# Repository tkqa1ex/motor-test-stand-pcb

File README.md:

# Motor Test Stand PCB

This repository contains the PCB design for a DC motor test stand.

## Features
- Current measurement (INA219 / ACS758)
- Temperature sensing (TMP117)
- Microcontroller interface (Arduino)

## Project Goal
Measure torque, efficiency, and electrical parameters of a DC motor using a generator-based load system.

## Files
- /pcb → PCB layout
- /schematic → circuit design
- /gerbers → manufacturing files

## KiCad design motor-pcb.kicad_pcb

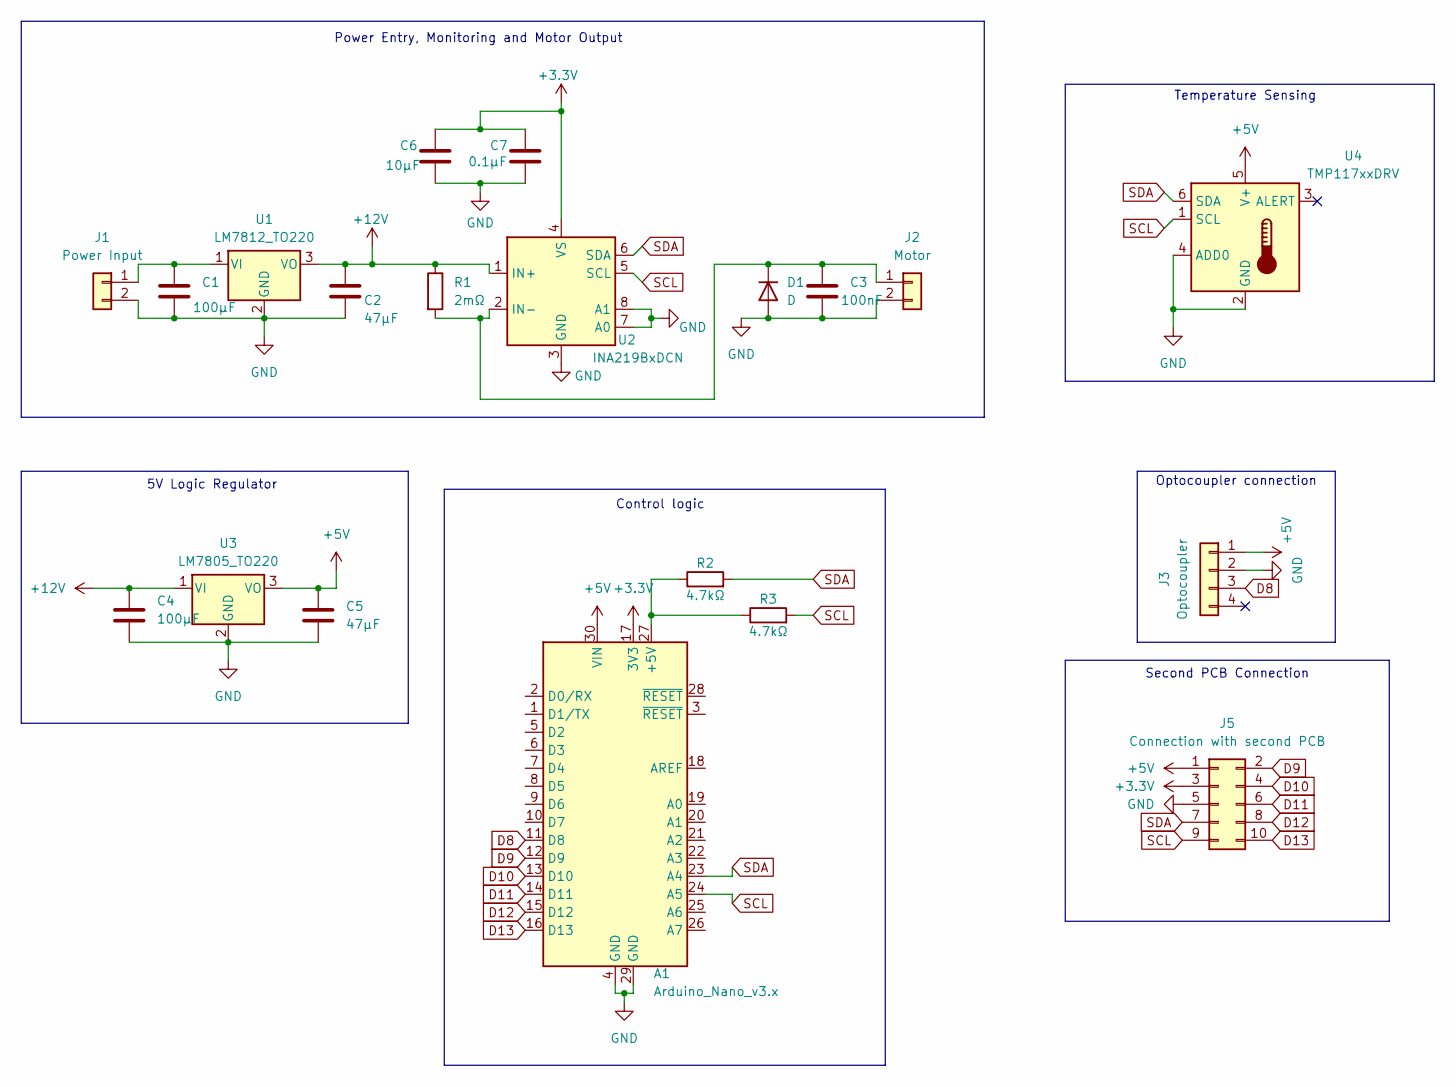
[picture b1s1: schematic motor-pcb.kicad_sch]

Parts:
A1: Arduino_Nano_v3.x; Arduino_Nano
C1, C4: 100µF; CP_Radial_D6.3mm_P2.50mm
C2, C5: 47µF; CP_Radial_D6.3mm_P2.50mm
C3: 100nF; C_Disc_D5.0mm_W2.5mm_P2.50mm
C6: 10µF; C_0805_2012Metric_Pad1.18x1.45mm_HandSolder
C7: 0.1µF; C_0805_2012Metric_Pad1.18x1.45mm_HandSolder
D1: D; D_DO-41_SOD81_P10.16mm_Horizontal
J1: Power Input; TerminalBlock_CUI_TB007-508-02_1x02_P5.08mm_Horizontal
J2: Motor; TerminalBlock_CUI_TB007-508-02_1x02_P5.08mm_Horizontal
J3: Optocoupler; PinHeader_1x04_P2.54mm_Vertical
J5: Connection with second PCB; PinHeader_2x05_P2.54mm_Vertical
R1: 2mΩ; R_2512_6332Metric_Pad1.40x3.35mm_HandSolder
R2, R3: 4.7kΩ; R_Axial_DIN0207_L6.3mm_D2.5mm_P7.62mm_Horizontal
U1: LM7812_TO220; TO-220-3_Vertical
U2: INA219BxDCN; SOT-23-8
U3: LM7805_TO220; TO-220-3_Vertical
U4: TMP117xxDRV; WSON-6-1EP_2x2mm_P0.65mm_EP1x1.6mm

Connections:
+3.3V: A1.17 (3V3), C6.1, C7.1, J5.3, U2.4 (VS)
+5V: A1.30 (VIN), C5.1, J3.1, J5.1, U3.3 (VO), U4.5 (V+)
+12V: C2.1, C4.1, R1.1, U1.3 (VO), U2.1 (IN+), U3.1 (VI)
D8: A1.11 (D8), J3.3
D9: A1.12 (D9), J5.2
D10: A1.13 (D10), J5.4
D11: A1.14 (D11), J5.6
D12: A1.15 (D12), J5.8
D13: A1.16 (D13), J5.10
GND: A1.4 (GND), A1.29 (GND), C1.2, C2.2, C3.2, C4.2, C5.2, C6.2, C7.2, D1.2 (A), J1.2, J2.2, J3.2, J5.5, U1.2 (GND), U2.3 (GND), U2.7 (A0), U2.8 (A1), U3.2 (GND), U4.2 (GND), U4.4 (ADD0)
unnamed: A1.27 (+5V), R2.1, R3.1
unnamed: C3.1, D1.1 (K), J2.1, R1.2, U2.2 (IN-)
unnamed: C1.1, J1.1, U1.1 (VI)
SCL: A1.24 (A5), J5.9, R3.2, U2.5 (SCL), U4.1 (SCL)
SDA: A1.23 (A4), J5.7, R2.2, U2.6 (SDA), U4.6 (SDA)

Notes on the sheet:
Temperature Sensing
Control logic
Optocoupler connection
Power Entry, Monitoring and Motor Output
Second PCB Connection
5V Logic Regulator

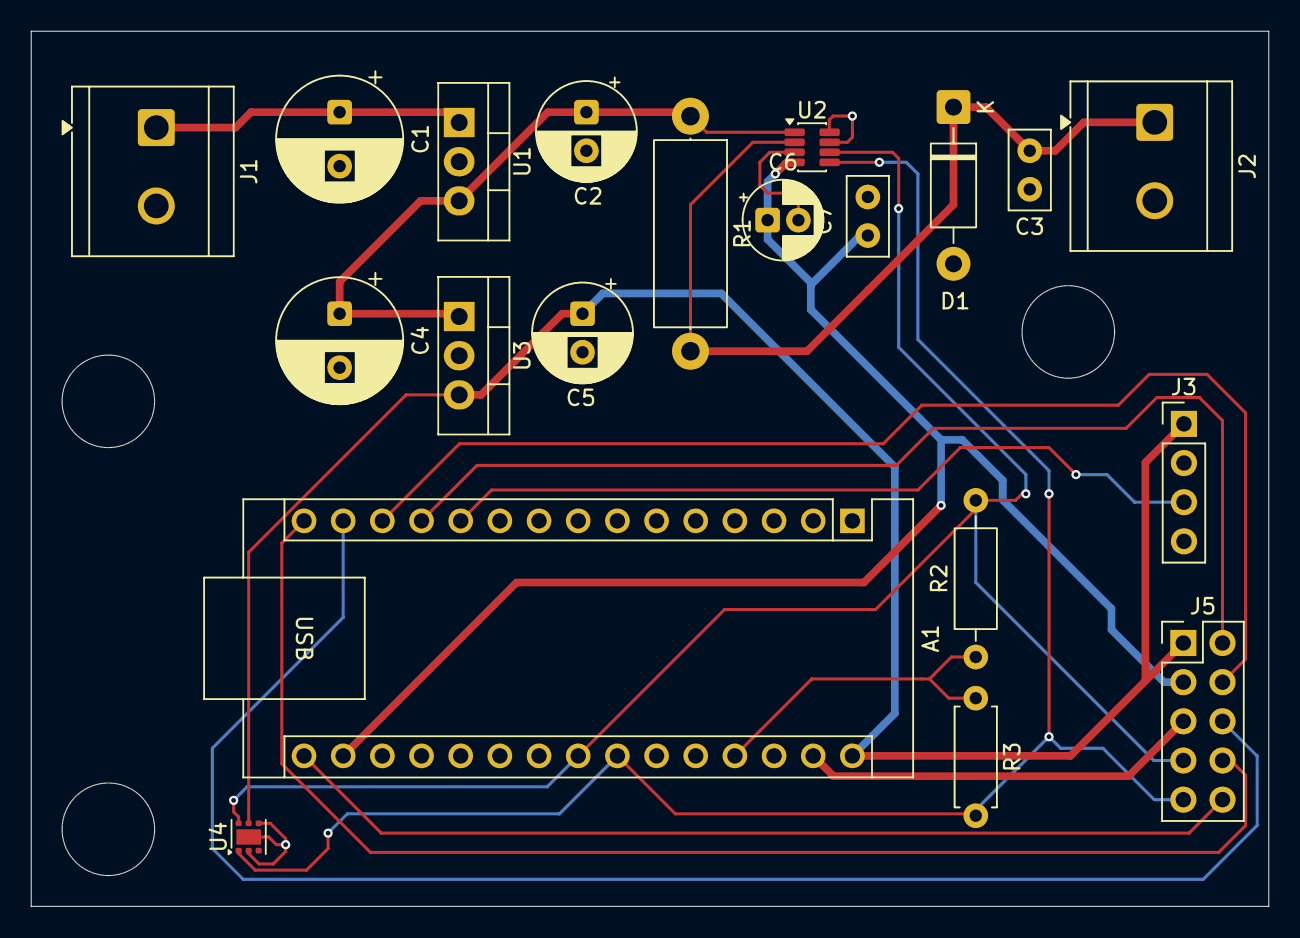
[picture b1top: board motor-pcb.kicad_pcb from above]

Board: 2 copper layers, 80.2 x 56.8 mm, 20 parts (0 on the bottom side), 15 nets.

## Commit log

2026-05-03 Update README with project information and features
    Added project details and features to README.
2026-05-03 Updated PCB layout: improved routing and component placement
2026-05-05 Updated shunt resistor value, footprints, layout
2026-05-11 Final Pcb
2026-05-11 Generator Board PCB
    Load control, Current and Voltage measures, Temperature measure
2026-05-11 Create Control-Board
2026-05-11 Create temp
2026-05-11 Moving files to control-board folder
2026-05-11 Create temp2
2026-05-11 Moving files to generator-board
